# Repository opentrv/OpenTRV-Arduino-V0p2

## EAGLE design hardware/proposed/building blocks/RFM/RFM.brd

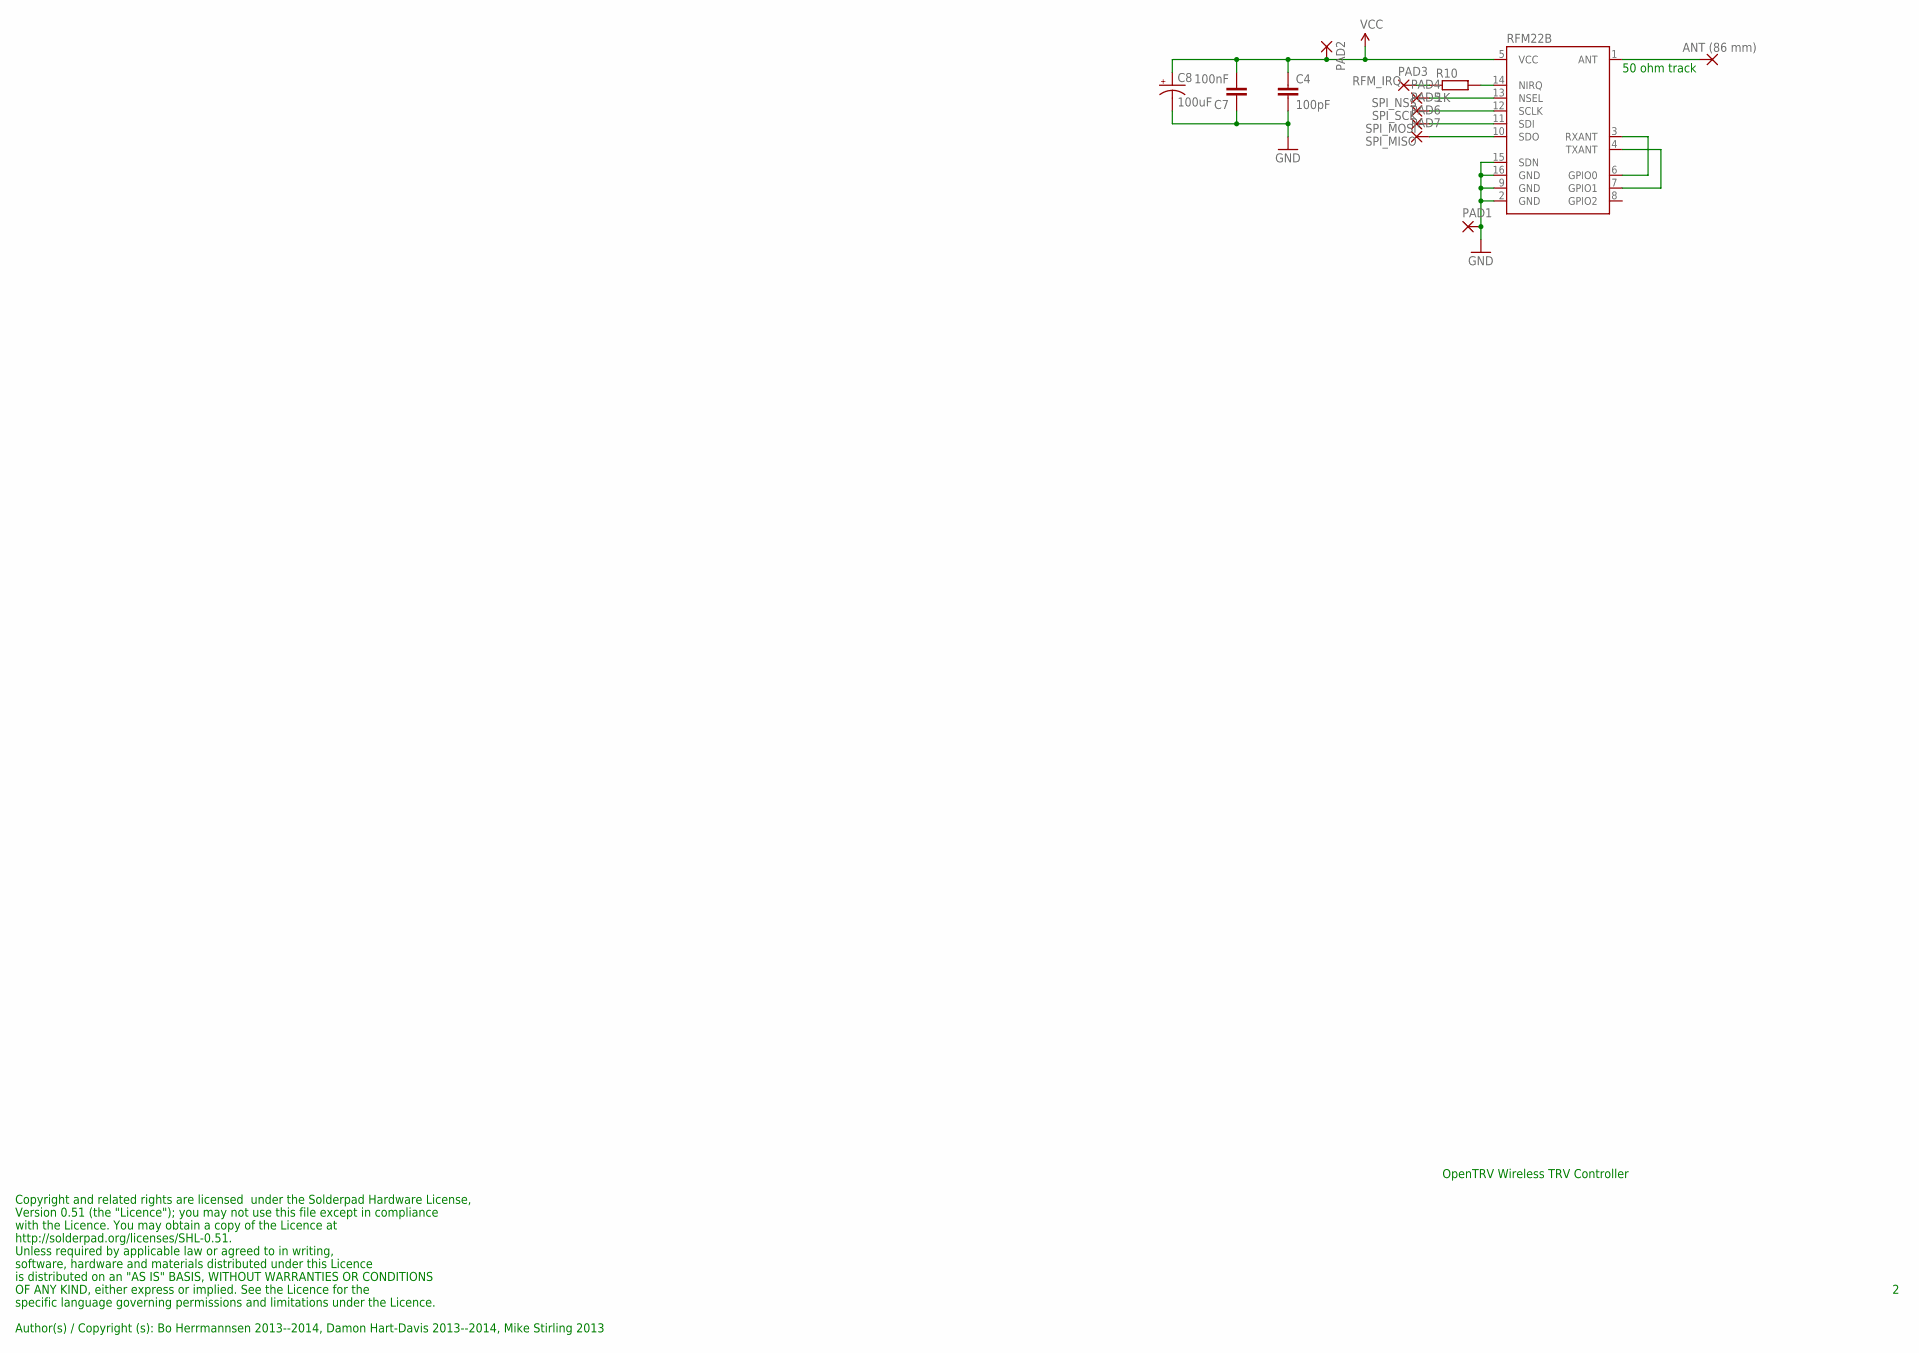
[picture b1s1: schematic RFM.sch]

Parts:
ANT: ANT (86 mm); 2,15/1,0
C4: 100pF; 0603-CAP
C7: 100nF; 0603-CAP
C8: 100uF; EIA3216
PAD1, PAD2, PAD3, PAD4, PAD5, PAD6, PAD7: 1,6/0,8
R10: 1K; R0603
RFM22B: RFM22SMD; RFM22-XXX-S2

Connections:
GND: C4.2, C7.1, C8.C (-), PAD1.1, RFM22B.2 (GND), RFM22B.9 (GND), RFM22B.15 (SDN), RFM22B.16 (GND)
unnamed: R10.2, RFM22B.14 (NIRQ)
unnamed: RFM22B.3 (RXANT), RFM22B.6 (GPIO0)
unnamed: RFM22B.4 (TXANT), RFM22B.7 (GPIO1)
unnamed: ANT.1, RFM22B.1 (ANT)
RFM_IRQ: PAD3.1, R10.1
SPI_MISO: PAD7.1, RFM22B.10 (SDO)
SPI_MOSI: PAD6.1, RFM22B.11 (SDI)
SPI_NSS: PAD4.1, RFM22B.13 (NSEL)
SPI_SCK: PAD5.1, RFM22B.12 (SCLK)
VCC: C4.1, C7.2, C8.A (+), PAD2.1, RFM22B.5 (VCC)

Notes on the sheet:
50 ohm track
Copyright and related rights are licensed under the Solderpad Hardware License,
Version 0.51 (the "Licence"); you may not use this file except in compliance
with the Licence. You may obtain a copy of the Licence at
http://solderpad.org/licenses/SHL-0.51.
Unless required by applicable law or agreed to in writing,
software, hardware and materials distributed under this Licence
is distributed on an "AS IS" BASIS, WITHOUT WARRANTIES OR CONDITIONS
Author(s) / Copyright (s): Bo Herrmannsen 2013--2014, Damon Hart-Davis 2013--2014, Mike Stirling 2013
OpenTRV Wireless TRV Controller
OF ANY KIND, either express or implied. See the Licence for the
specific language governing permissions and limitations under the Licence.

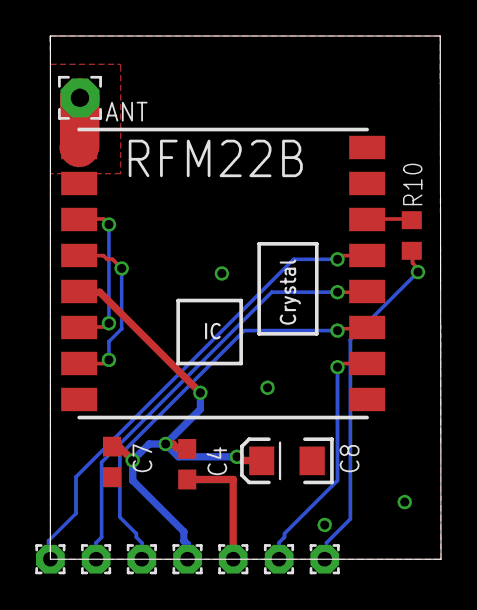
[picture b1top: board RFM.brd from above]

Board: 2 copper layers, 21.7 x 29.1 mm, 13 parts (0 on the bottom side), 11 nets.

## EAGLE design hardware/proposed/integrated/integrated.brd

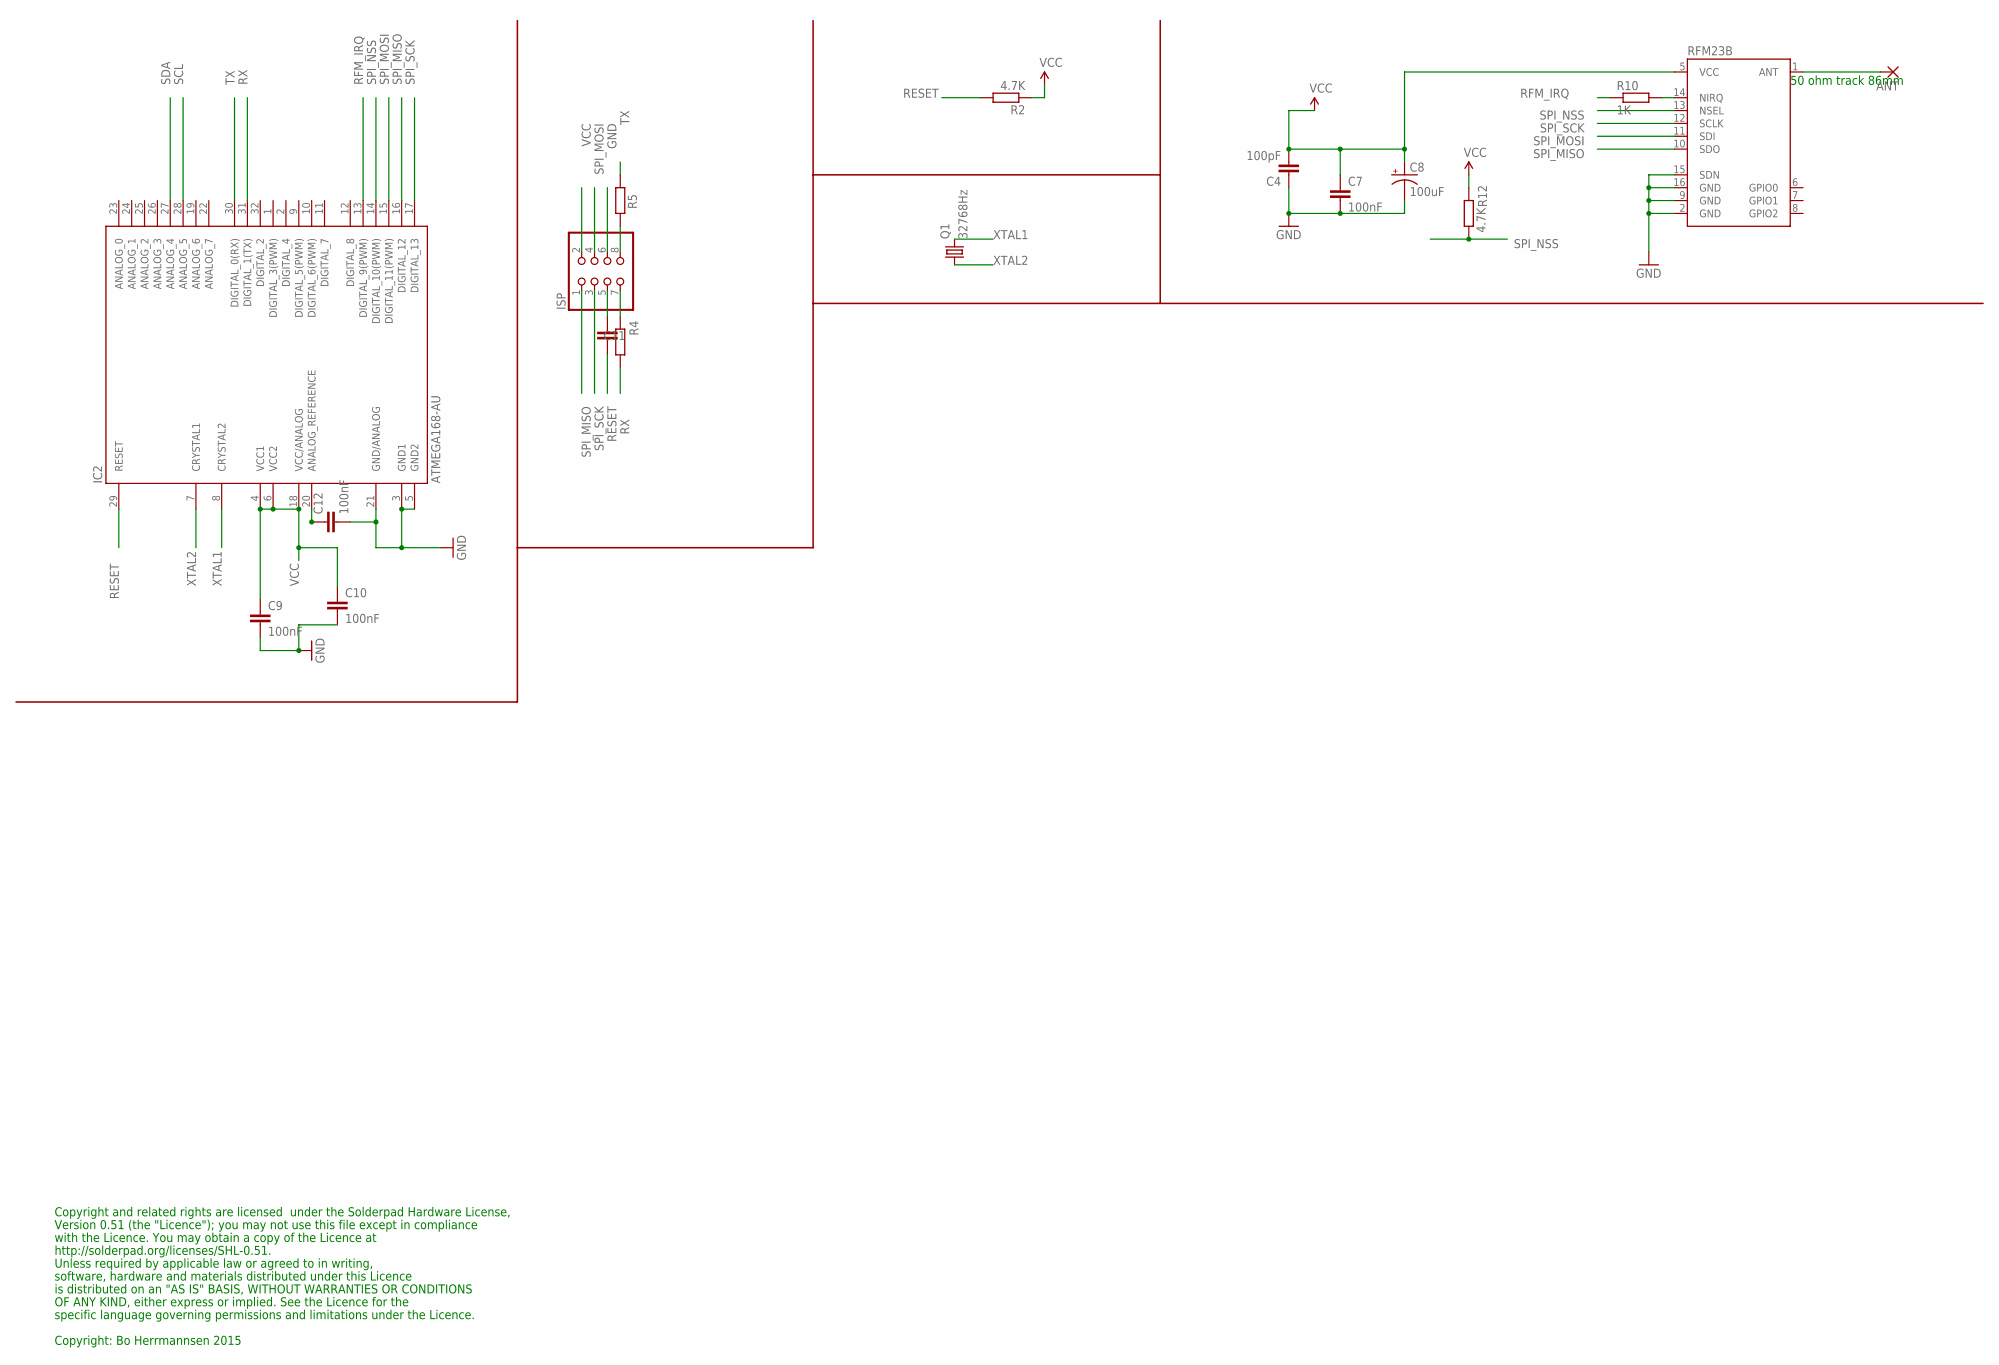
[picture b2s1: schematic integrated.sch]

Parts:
ANT: 2,15/1,0
C4: 100pF; C0603
C7, C9, C10, C11, C12: 100nF; C0603
C8: 100uF; EIA3216
IC2: ATMEGA168-AU; TQFP32-08
ISP: PINHD-2X4/90; 2X04/90
Q1: 32768Hz; MC-306
R2, R4, R5, R12: 4.7K; R0603
R10: 1K; R0603
RFM23B: RFM23B; RFM23-XXX-S1

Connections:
GND: C4.1, C7.2, C8.C (-), C9.2, C10.2, C12.2, IC2.3 (GND1), IC2.5 (GND2), IC2.21 (GND/ANALOG), ISP.6, RFM23B.2 (GND), RFM23B.9 (GND), RFM23B.15 (SDN), RFM23B.16 (GND)
unnamed: C11.2, ISP.5
unnamed: ISP.8, R5.2
unnamed: ISP.7, R4.2
unnamed: C12.1, IC2.20 (ANALOG_REFERENCE)
unnamed: R10.2, RFM23B.14 (NIRQ)
unnamed: ANT.1, RFM23B.1 (ANT)
RESET: C11.1, IC2.29 (RESET), R2.2
RFM_IRQ: IC2.13 (DIGITAL_9(PWM)), R10.1
RX: IC2.31 (DIGITAL_1(TX)), R4.1
SCL: IC2.28 (ANALOG_5)
SDA: IC2.27 (ANALOG_4)
SPI_MISO: IC2.16 (DIGITAL_12), ISP.1, RFM23B.10 (SDO)
SPI_MOSI: IC2.15 (DIGITAL_11(PWM)), ISP.4, RFM23B.11 (SDI)
SPI_NSS: IC2.14 (DIGITAL_10(PWM)), R12.1, RFM23B.13 (NSEL)
SPI_SCK: IC2.17 (DIGITAL_13), ISP.3, RFM23B.12 (SCLK)
TX: IC2.30 (DIGITAL_0(RX)), R5.1
VCC: C4.2, C7.1, C8.A (+), C9.1, C10.1, IC2.4 (VCC1), IC2.6 (VCC2), IC2.18 (VCC/ANALOG), ISP.2, R2.1, R12.2, RFM23B.5 (VCC)
XTAL1: IC2.8 (CRYSTAL2), Q1.4 (2)
XTAL2: IC2.7 (CRYSTAL1), Q1.1

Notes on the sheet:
Copyright and related rights are licensed under the Solderpad Hardware License,
Version 0.51 (the "Licence"); you may not use this file except in compliance
with the Licence. You may obtain a copy of the Licence at
http://solderpad.org/licenses/SHL-0.51.
Unless required by applicable law or agreed to in writing,
software, hardware and materials distributed under this Licence
is distributed on an "AS IS" BASIS, WITHOUT WARRANTIES OR CONDITIONS
OF ANY KIND, either express or implied. See the Licence for the
specific language governing permissions and limitations under the Licence.
50 ohm track 86mm
Copyright: Bo Herrmannsen 2015

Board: 2 copper layers, 17 parts (9 on the bottom side), 18 nets, no tracks yet.

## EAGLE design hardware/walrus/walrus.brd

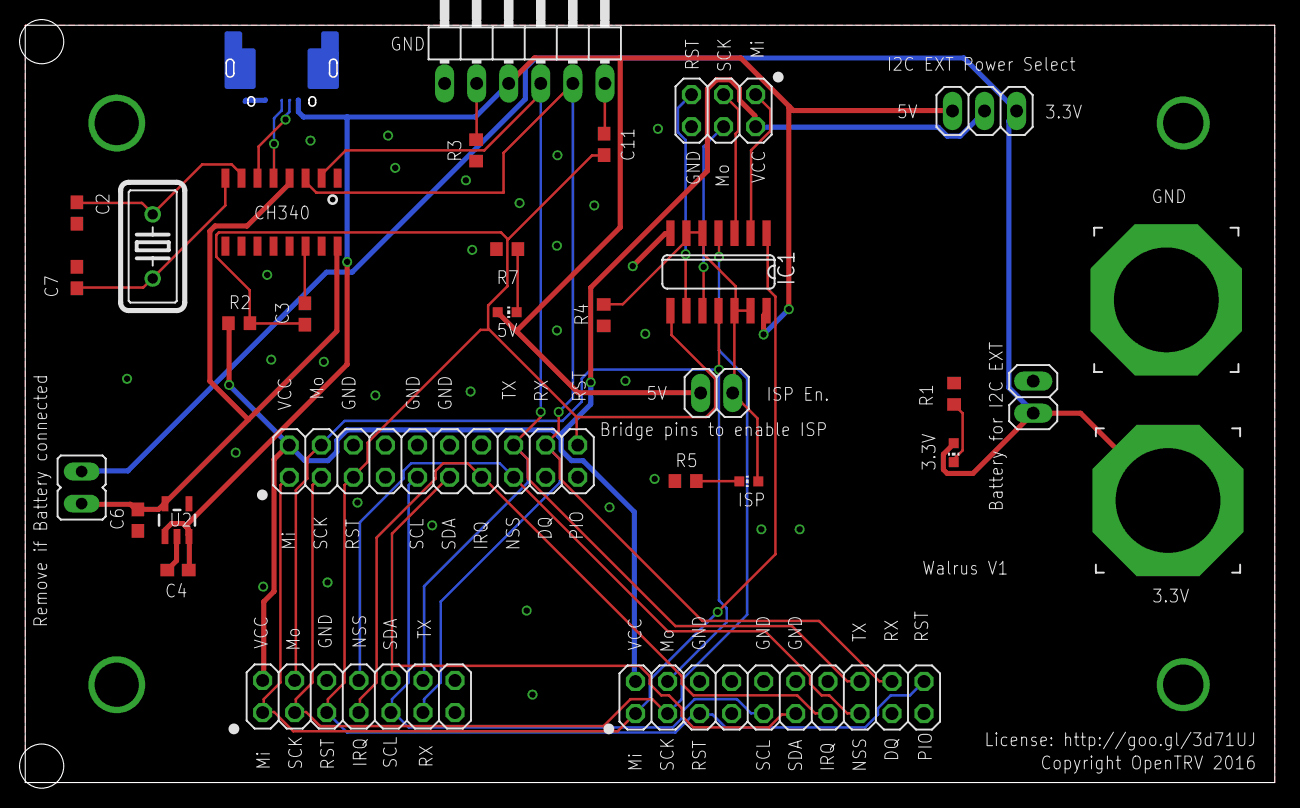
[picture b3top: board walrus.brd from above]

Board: 2 copper layers, 99.0 x 60.0 mm, 31 parts (1 on the bottom side), 30 nets.

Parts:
3.3V: 3,81/1,4
12MHZ: HC18U-V
C2, C7: 22pF; C0603
C3, C11: 100nF; 0603-CAP
C4, C6: 10uF 10V; 0603-CAP
FTDI: 1X06/90
GND: 3,81/1,4
I2C_EXT, I2C_EXT2: 2X10
I2C_EXT1: 2X07
IC1: 4066D; SO14
ISP: 2X03
JP1: JP1
JP2, JP4: 1X02
JP3: 1X03
LED, LED1, LED2: CHIP-LED0603
R1, R5, R7: 470R; R0603
R2, R4: 10K; R0603
R3: 4K7; R0603
U2: TC1185SMD; TC1185
U$3: CH340G; SOIC16
USBPOWER: MICRO-USB-FCI-10103592

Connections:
3.3V: 3.3V.1, JP1.1, JP2.1, JP3.1, LED1.A
5V: C4.1, FTDI.3, IC1.14, JP3.3, JP4.2, LED.A, U2.1, U2.3, USBPOWER.1
D+: U$3.5, USBPOWER.3
D-: U$3.6, USBPOWER.2
GND: C2.2, C4.2, C6.1, C7.2, FTDI.1, GND.1, I2C_EXT.6, I2C_EXT.10, I2C_EXT.12, I2C_EXT1.6, I2C_EXT2.6, I2C_EXT2.10, I2C_EXT2.12, IC1.7, ISP.6, JP2.2, R1.1, R3.1, R4.1, R5.1, R7.1, U2.2, U$3.1, USBPOWER.5, USBPOWER.7, USBPOWER.17
ISP_SW: IC1.5, IC1.6, IC1.12, IC1.13, JP4.1, LED2.A, R4.2
unnamed: C11.2, FTDI.6
unnamed: C3.2, U$3.14
unnamed: FTDI.2, R3.2
unnamed: IC1.2, ISP.1
unnamed: LED1.C, R1.2
unnamed: 12MHZ.1, C2.1, U$3.7
unnamed: IC1.3, ISP.3
unnamed: LED.C, R7.2
unnamed: C6.2, JP1.2, U2.5, U$3.4, U$3.16
unnamed: 12MHZ.2, C7.1, U$3.8
unnamed: IC1.9, ISP.5
unnamed: IC1.10, ISP.4
unnamed: LED2.C, R5.2
RESET: C3.1, C11.1, I2C_EXT.5, I2C_EXT.20, I2C_EXT1.5, I2C_EXT2.5, I2C_EXT2.20, IC1.8, R2.2
RFM_IRQ: I2C_EXT.13, I2C_EXT1.7, I2C_EXT2.13
RX: FTDI.5, I2C_EXT.18, I2C_EXT1.11, I2C_EXT2.18, U$3.3
SCL: I2C_EXT.9, I2C_EXT1.9, I2C_EXT2.9
SDA: I2C_EXT.11, I2C_EXT1.10, I2C_EXT2.11
SPI_MISO: I2C_EXT.1, I2C_EXT1.1, I2C_EXT2.1, IC1.1
SPI_MOSI: I2C_EXT.4, I2C_EXT1.4, I2C_EXT2.4, IC1.11
SPI_NSS: I2C_EXT.15, I2C_EXT1.8, I2C_EXT2.15
SPI_SCK: I2C_EXT.3, I2C_EXT1.3, I2C_EXT2.3, IC1.4
TX: FTDI.4, I2C_EXT.16, I2C_EXT1.12, I2C_EXT2.16, U$3.2
VCC: I2C_EXT.2, I2C_EXT1.2, I2C_EXT2.2, ISP.2, JP3.2, R2.1

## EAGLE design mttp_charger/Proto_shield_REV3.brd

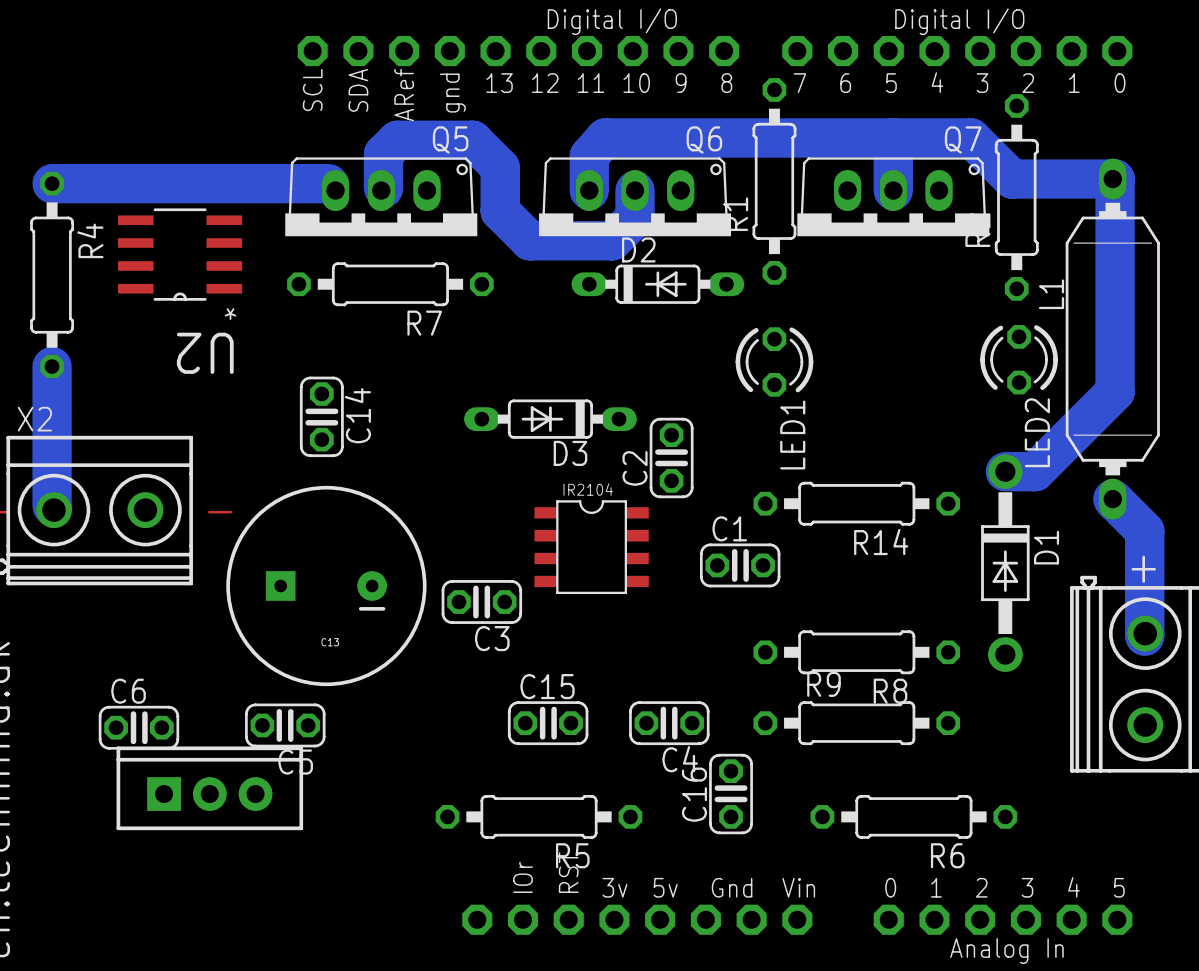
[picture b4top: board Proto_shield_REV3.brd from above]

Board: 2 copper layers, 34 parts (0 on the bottom side), 21 nets.

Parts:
C1, C4, C16: 100nF; C025-024X044
C2, C3, C5, C6, C14, C15: 100 nF; C025-024X044
C13: 100uF; CPOL-RADIAL-1000UF-25V
D1: UF4007; DO41-10
D2, D3: 1N4148; DO35-7
IC1: TO220-IGO
L1: 33uH; SUKW1-17
LED1, LED2: LED3MM
Q5, Q6, Q7: TO220V
R1, R2: 0207/10
R4: 0.005 ohm; 0207/10
R5, R8: 10K 1%; 0207/10
R6, R9: 2K2 1%; 0207/10
R7: 470K 1%; 0207/10
R14: 200; 0207/10
U1: ARDUINOR3-BPLACE
U2: MAX4172ESA+; SOIC127P600X175-8N
U$1: IR2104S
X1: Battery 12 volt; MKDSN1,5/2-5,08
X2: Solarpanel 20 volt; MKDSN1,5/2-5,08

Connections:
GND: C3.1, C4.2, C5.2, C6.2, C13.2, C14.2, C15.2, C16.2, D1.A, IC1.GND, LED1.K, LED2.K, Q7.3, R6.1, R9.1, U1.GND, U1.GND1, U1.GND2, U2.3, U$1.4, X1.2, X2.2
unnamed: U1.D9, U$1.2
unnamed: D2.C, Q5.1, R7.1
unnamed: C5.1, C15.1, IC1.OUT, U1.5V, U2.1
unnamed: C16.1, R5.1, R6.2, U1.A0
unnamed: C1.1, C2.2, D1.C, L1.1, Q6.3, Q7.2, U$1.6
unnamed: U1.D8, U$1.3
unnamed: C1.2, R14.2
unnamed: C4.1, R8.1, R9.2, U1.A2
unnamed: Q5.2, Q6.2
unnamed: Q7.1, U$1.5
unnamed: C2.1, D3.C, U$1.8
unnamed: R2.2, U1.D6
unnamed: C6.1, IC1.IN, R4.2, R5.2, U2.8, X2.1
unnamed: LED2.A, R2.1
unnamed: LED1.A, R1.1
unnamed: R1.2, U1.D7
unnamed: L1.2, R8.2, R14.1, X1.1
unnamed: C14.1, U1.A1, U2.4
unnamed: D2.A, Q6.1, U$1.7
unnamed: C3.2, C13.1, D3.A, Q5.3, R4.1, R7.2, U2.6, U$1.1

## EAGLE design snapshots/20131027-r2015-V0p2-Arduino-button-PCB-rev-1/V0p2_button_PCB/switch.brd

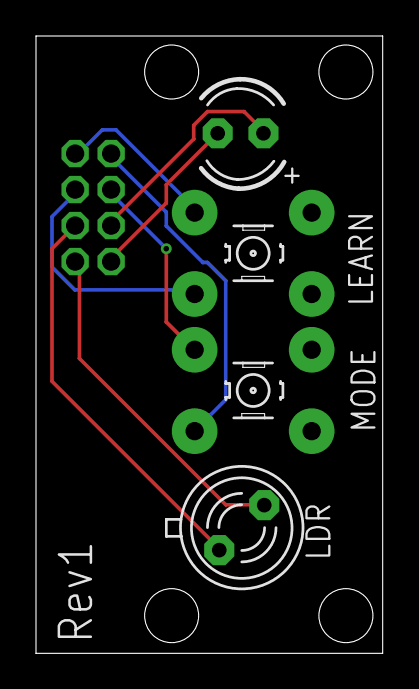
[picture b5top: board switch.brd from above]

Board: 2 copper layers, 19.3 x 34.3 mm, 5 parts (1 on the bottom side), 8 nets.

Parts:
JP10: 2X04
LDR: BPX65
LEARN: B3F-10XX
LED1: LED3MM
MODE: B3F-10XX

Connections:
unnamed: JP10.1, MODE.2
unnamed: JP10.4, LEARN.2
unnamed: JP10.2, LEARN.4
unnamed: JP10.3, MODE.4
unnamed: JP10.7, LED1.K
unnamed: JP10.5, LED1.A
unnamed: JP10.6, LDR.A
unnamed: JP10.8, LDR.K

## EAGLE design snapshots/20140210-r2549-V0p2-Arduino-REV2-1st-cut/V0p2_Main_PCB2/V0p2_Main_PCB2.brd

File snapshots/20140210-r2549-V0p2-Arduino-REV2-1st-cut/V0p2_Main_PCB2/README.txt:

Using ATmega pinout for Eagle from:
http://www.faludi.com/2008/10/07/arduino-avr-library-for-eagle-layout-editor/
without explicit licence but following email permission:

    From: Rob Faludi
    Date: 13 May 2013 00:34:52 GMT+01:00
    Subject: Re: A comment from Damon Hart-Davis
    
    Sure, go for it!
    
    A new submission (form: "Contact Form")
    ============================================
    Submitted on: May 12, 2013
    Via: /contact/
    
    --------------------------Contact Me----------------------
    
    Your Name:                      Damon Hart-Davis
    
    Message:                      
    May we use your Eagle ATmega package/library:
    
    http://www.faludi.com/2008/10/07/arduino-avr-library-for-eagle-layout-editor/
    
    In our Apache/Solderpad-licenced OpenTRV project please?
    
    Rgds
    
    Damon
    http://opentrv.org.uk/

Note ITEADstudio .dru and .cam files downloaded from their site AND NOT COVERED BY OUR APACHE LICENCE
though ITEADstudio would probably be happy for you to use their service like we did!

Component-ordering document, REV0:
https://docs.google.com/spreadsheet/ccc?key=0AkWwv0Q6wTaZdHkyZ0JmMVE3X1ExWGNqcHVxUUhROHc#gid=0

REV1:
https://docs.google.com/spreadsheet/ccc?key=0AkWwv0Q6wTaZdGZCcmlXR25tT0YwWmFfb1RUaDgtZUE&usp=drive_web#gid=0

REV2:
https://docs.google.com/spreadsheet/ccc?key=0AkWwv0Q6wTaZdGhGU29kemRXN3pGTXhGcWNnMnRyMVE&usp=sharing#gid=0

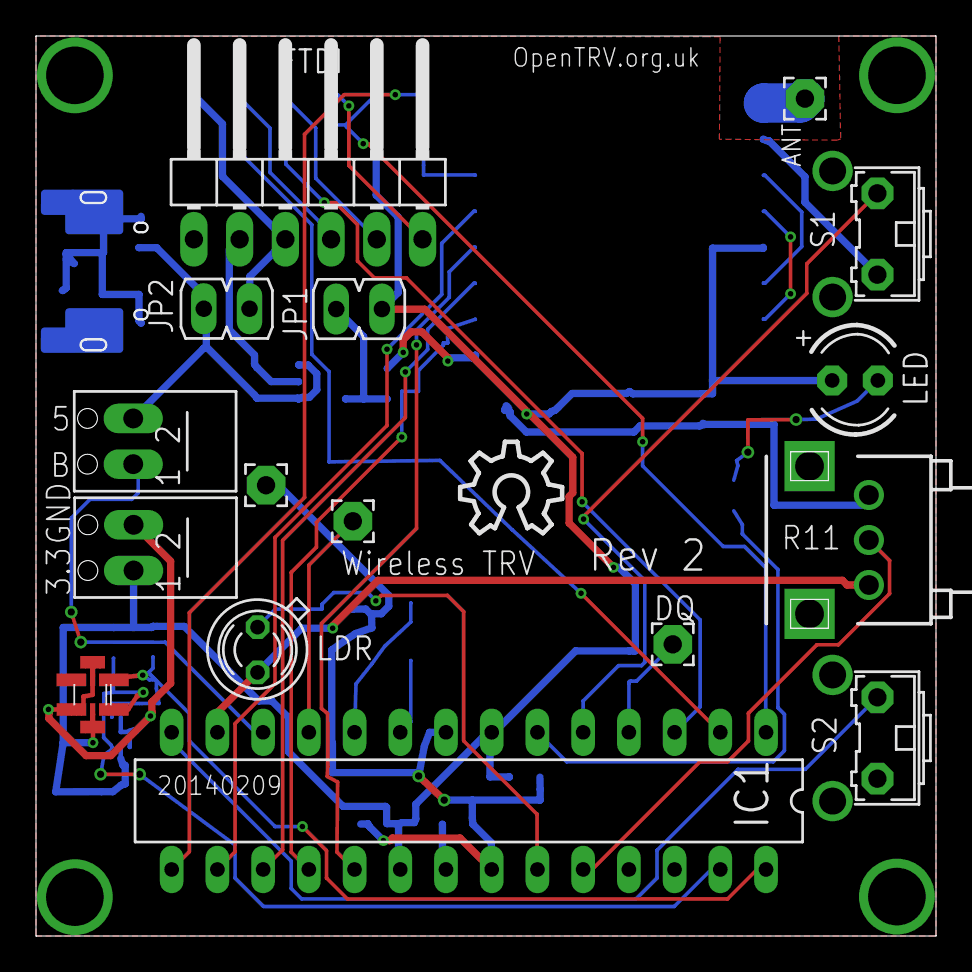
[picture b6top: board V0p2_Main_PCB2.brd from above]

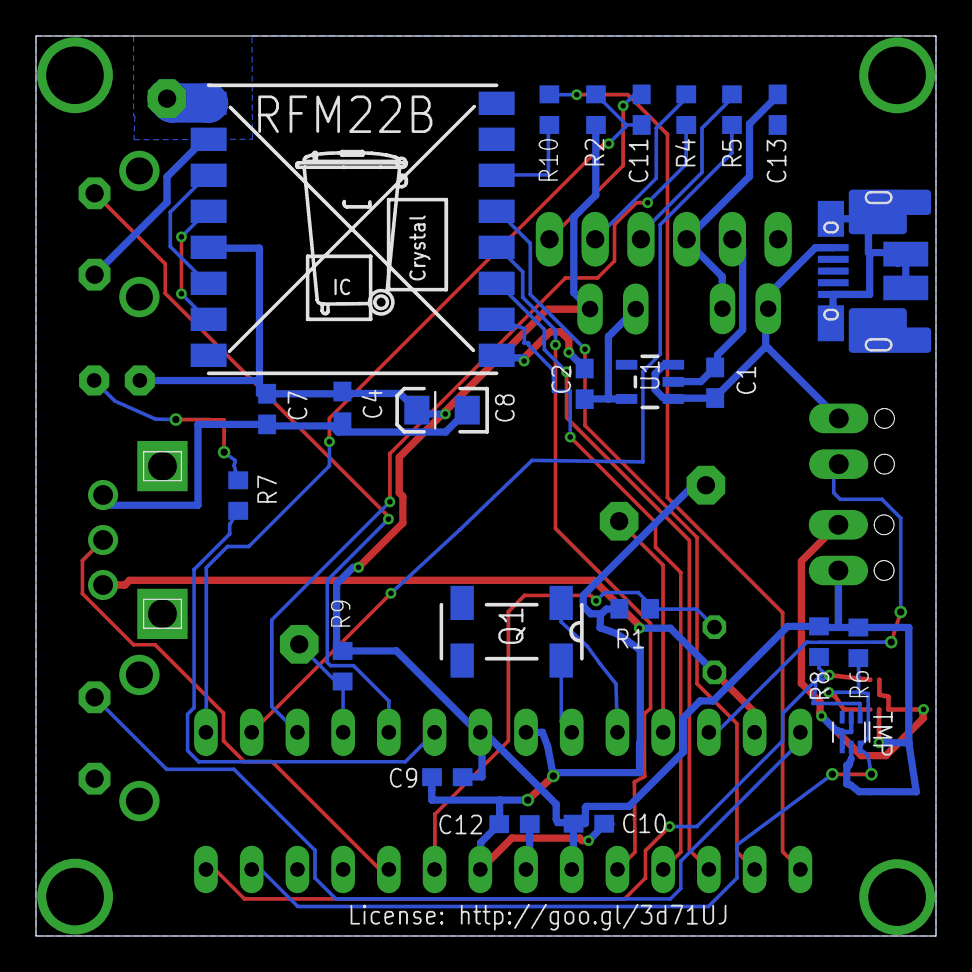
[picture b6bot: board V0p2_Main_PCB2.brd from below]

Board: 2 copper layers, 50.0 x 50.0 mm, 42 parts (25 on the bottom side), 35 nets.

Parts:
ANT: ANT (86 mm); 2,15/1,0
C1, C2, C13: 10uF 10V; 0603-CAP
C4: 100pF; 0603-CAP
C7, C9, C10, C11, C12: 100nF; 0603-CAP
C8: 100uF; EIA3216
DQ: 2,15/1,0
FTDI: 1X06/90
IC1: ATMEGA328P-PU; DIL28-3
JP1, JP2: JP1
LDR: BPX65
LED: LED3MM
MODE, MODE1: 2,15/1,0
Q1: 32768Hz; MC-306
R1: 100K; R0603
R2, R4, R5: 10K; R0603
R6, R8: 4K7; R0603
R7: 470R; R0603
R9: 4.7K; R0603
R10: 1K; R0603
R11: EVUE2A; EVUE
RFM22B: RFM22SMD; RFM22-XXX-S2
S1, S2: B3F-31XX
TMP: TMP112
U1: TC1185SMD; TC1185
U$1: OSHW_10X200_NOTEXT
U$2: TONNE
U$3: TMP; TMP112
USBPOWER: MICRO-USB-FCI-10103592
X1, X2: SCREWTERMINAL

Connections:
5V: C1.1, JP2.2, U1.1, U1.3, USBPOWER.1, X1.2
AI1: IC1.24, R11.2
BOILER: IC1.12, X1.1
BUTTON_LEARN2_L: IC1.5, S1.2
BUTTON_LEARN_L: IC1.14, S2.2
BUTTON_MODE_L: IC1.11, MODE1.1
D2: DQ.1, IC1.4, R9.1
GND: C1.2, C2.1, C4.2, C7.1, C8.C, C9.2, C10.2, C12.2, C13.1, FTDI.1, FTDI.2, IC1.8, IC1.22, MODE.1, R1.2, R11.3, RFM22B.2, RFM22B.9, RFM22B.15, RFM22B.16, S1.1, S2.1, TMP.2, TMP.4, U1.2, U$3.2, U$3.4, USBPOWER.5, USBPOWER.7, USBPOWER.11, USBPOWER.12, USBPOWER.17, X2.2
IO_POWER_UP: IC1.13, LDR.K, R11.1
LDR: IC1.23, LDR.A, R1.1
LED_HEATCALL_L: IC1.6, R7.1
unnamed: C11.2, FTDI.6
unnamed: FTDI.4, R5.2
unnamed: FTDI.5, R4.2
unnamed: C12.1, IC1.21
unnamed: R10.2, RFM22B.14
unnamed: C2.2, JP1.1, U1.5
unnamed: C13.2, FTDI.3, JP2.1
unnamed: LED.K, R7.2
unnamed: RFM22B.3, RFM22B.6
unnamed: RFM22B.4, RFM22B.7
unnamed: ANT.1, RFM22B.1
RESET: C11.1, IC1.1, R2.2
RFM_IRQ: IC1.15, R10.1
RX: IC1.3, R4.1
SCL: IC1.28, R8.1, TMP.1, U$3.1
SDA: IC1.27, R6.2, TMP.6, U$3.6
SPI_MISO: IC1.18, RFM22B.10
SPI_MOSI: IC1.17, RFM22B.11
SPI_NSS: IC1.16, RFM22B.13
SPI_SCK: IC1.19, RFM22B.12
TX: IC1.2, R5.1
VCC: C4.1, C7.2, C8.A, C9.1, C10.1, IC1.7, IC1.20, JP1.2, LED.A, R2.1, R6.1, R8.2, R9.2, RFM22B.5, TMP.5, U$3.5, X2.1
XTAL1: IC1.9, Q1.4
XTAL2: IC1.10, Q1.1

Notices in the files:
hardware/walrus/walrus.brd:
Copyright OpenTRV 2016
License: http://goo.gl/3d71UJ
parts and their libraries:
SparkFun-Passives: Licensing: CC v3.0 Share-Alike You are welcome to use this library for commercial purposes.
SparkFun-Capacitors: Licensing: Creative Commons ShareAlike 4.0 International - https://creativecommons.org/licenses/by-sa/4.0
